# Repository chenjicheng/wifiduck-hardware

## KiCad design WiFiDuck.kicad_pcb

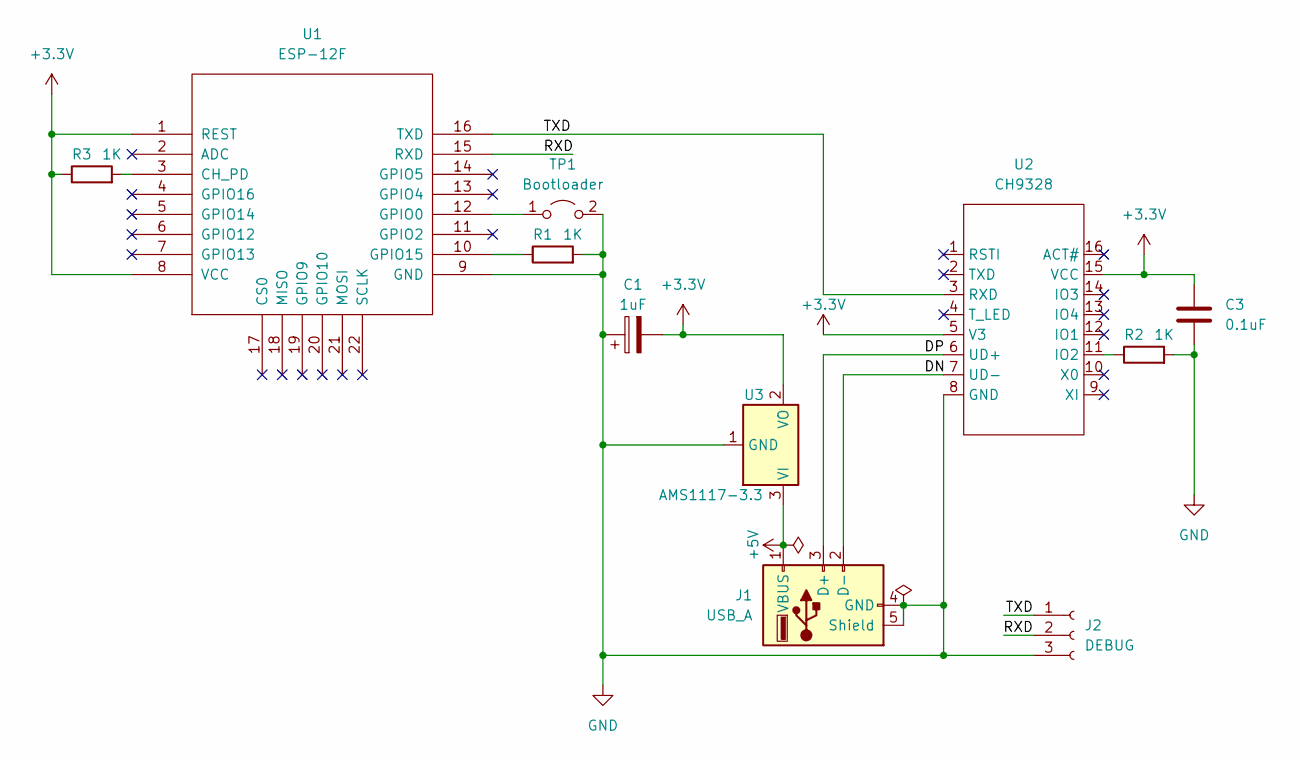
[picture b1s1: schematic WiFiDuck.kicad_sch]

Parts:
C1: 1uF; CP_EIA-3216-18_Kemet-A_Pad1.58x1.35mm_HandSolder
C3: 0.1uF; R_0603_1608Metric_Pad0.98x0.95mm_HandSolder
J1: USB_A; USB-A_Plug_AM_90_THT
J2: DEBUG; PinHeader_1x03_P2.54mm_Vertical
R1, R2, R3: 1K; R_0603_1608Metric_Pad0.98x0.95mm_HandSolder
TP1: Bootloader; SolderJumper-2_P1.3mm_Open_TrianglePad1.0x1.5mm
U1: ESP-12F; ESP-12E_SMD
U2: CH9328; SOP-16_3.9x9.9mm_P1.27mm
U3: AMS1117-3.3; SOT-223-3_TabPin2

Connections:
+3.3V: C1.2, C3.1, R3.1, U1.1 (REST), U1.8 (VCC), U2.5 (V3), U2.15 (VCC), U3.2 (VO)
+5V: J1.1 (VBUS), U3.3 (VI)
/DN: J1.2 (D-), U2.7 (UD-)
/DP: J1.3 (D+), U2.6 (UD+)
/RXD: J2.2, U1.15 (RXD)
/TXD: J2.1, U1.16 (TXD), U2.3 (RXD)
GND: C1.1, C3.2, J1.4 (GND), J1.5 (Shield), J2.3, R1.2, R2.2, TP1.2 (B), U1.9 (GND), U2.8 (GND), U3.1 (GND)
unnamed: TP1.1 (A), U1.12 (GPIO0)
unnamed: R3.2, U1.3 (CH_PD)
unnamed: R1.1, U1.10 (GPIO15)
unnamed: R2.1, U2.11 (IO2)

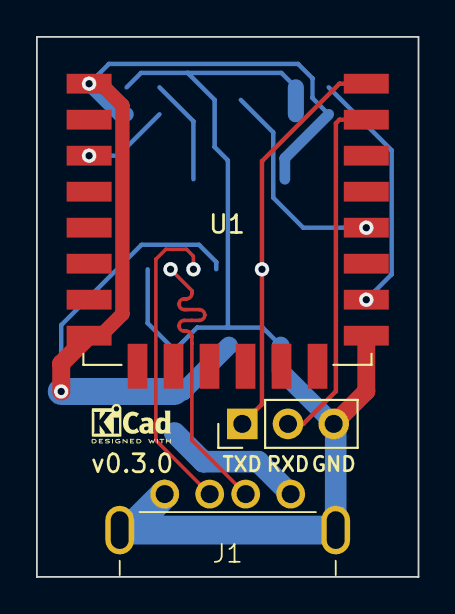
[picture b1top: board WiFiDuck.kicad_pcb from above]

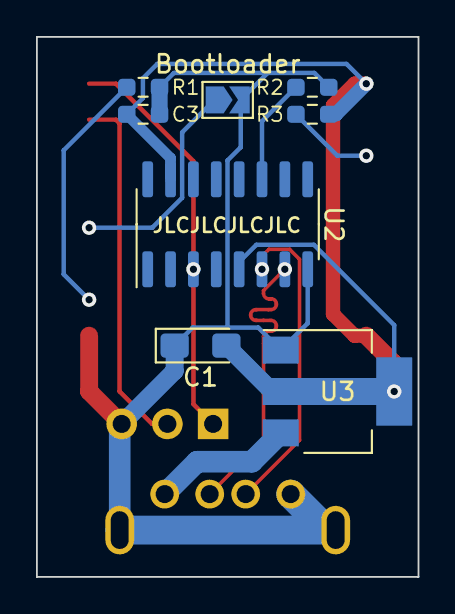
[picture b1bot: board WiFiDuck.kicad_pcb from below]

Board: 2 copper layers, 21.2 x 30.0 mm, 11 parts (8 on the bottom side), 11 nets.

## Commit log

2023-10-29 v0.1.0
2023-11-05 v0.2.0
    Fix CH9328 footprint
2023-11-05 Add JLC customer number
2023-11-18 Move bom to docs
2023-12-21 v0.3.0
    Fix USB-A
